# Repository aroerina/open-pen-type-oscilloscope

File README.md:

# open-pen-type-oscilloscope

ペンタイプオシロスコープ用の KiCad 基板設計データです。回路やスペックはDroidOscilloを踏襲しています。

このリポジトリには、回路図、PCB レイアウト、カスタムシンボル、カスタムフットプリント、3D モデル、製造用データを含みます。

.

## 概要

- KiCad プロジェクト: `USB_Oscilloscope.kicad_pro`
- 回路図: `USB_Oscilloscope.kicad_sch`
- PCB レイアウト: `USB_Oscilloscope.kicad_pcb`

- カスタムライブラリ: `ps_lib/`

## 関連リポジトリ

- ファームウェア: https://github.com/aroerina/DroidOscillo-Firmaware
- Android ホストアプリ: https://github.com/aroerina/DroidOscillo-Android_host
- 基板リポジトリ: https://github.com/aroerina/DoroidOscillo-Board

## 公開データ

回路図やガーバーファイルは、以下の Release ページにあります。

- https://github.com/aroerina/open-pen-type-oscilloscope/releases/tag/rev2.0

## 注意事項

- ファームウェア書き込みテストはまだ行っていません。かなり投げやり状態です。
- 製造や実装を行う前に、回路図、PCB、部品表、製造データを必ず確認してください。

## ライセンス

このハードウェア設計データは CERN Open Hardware Licence Version 2 - Permissive（CERN-OHL-P）で公開されています。

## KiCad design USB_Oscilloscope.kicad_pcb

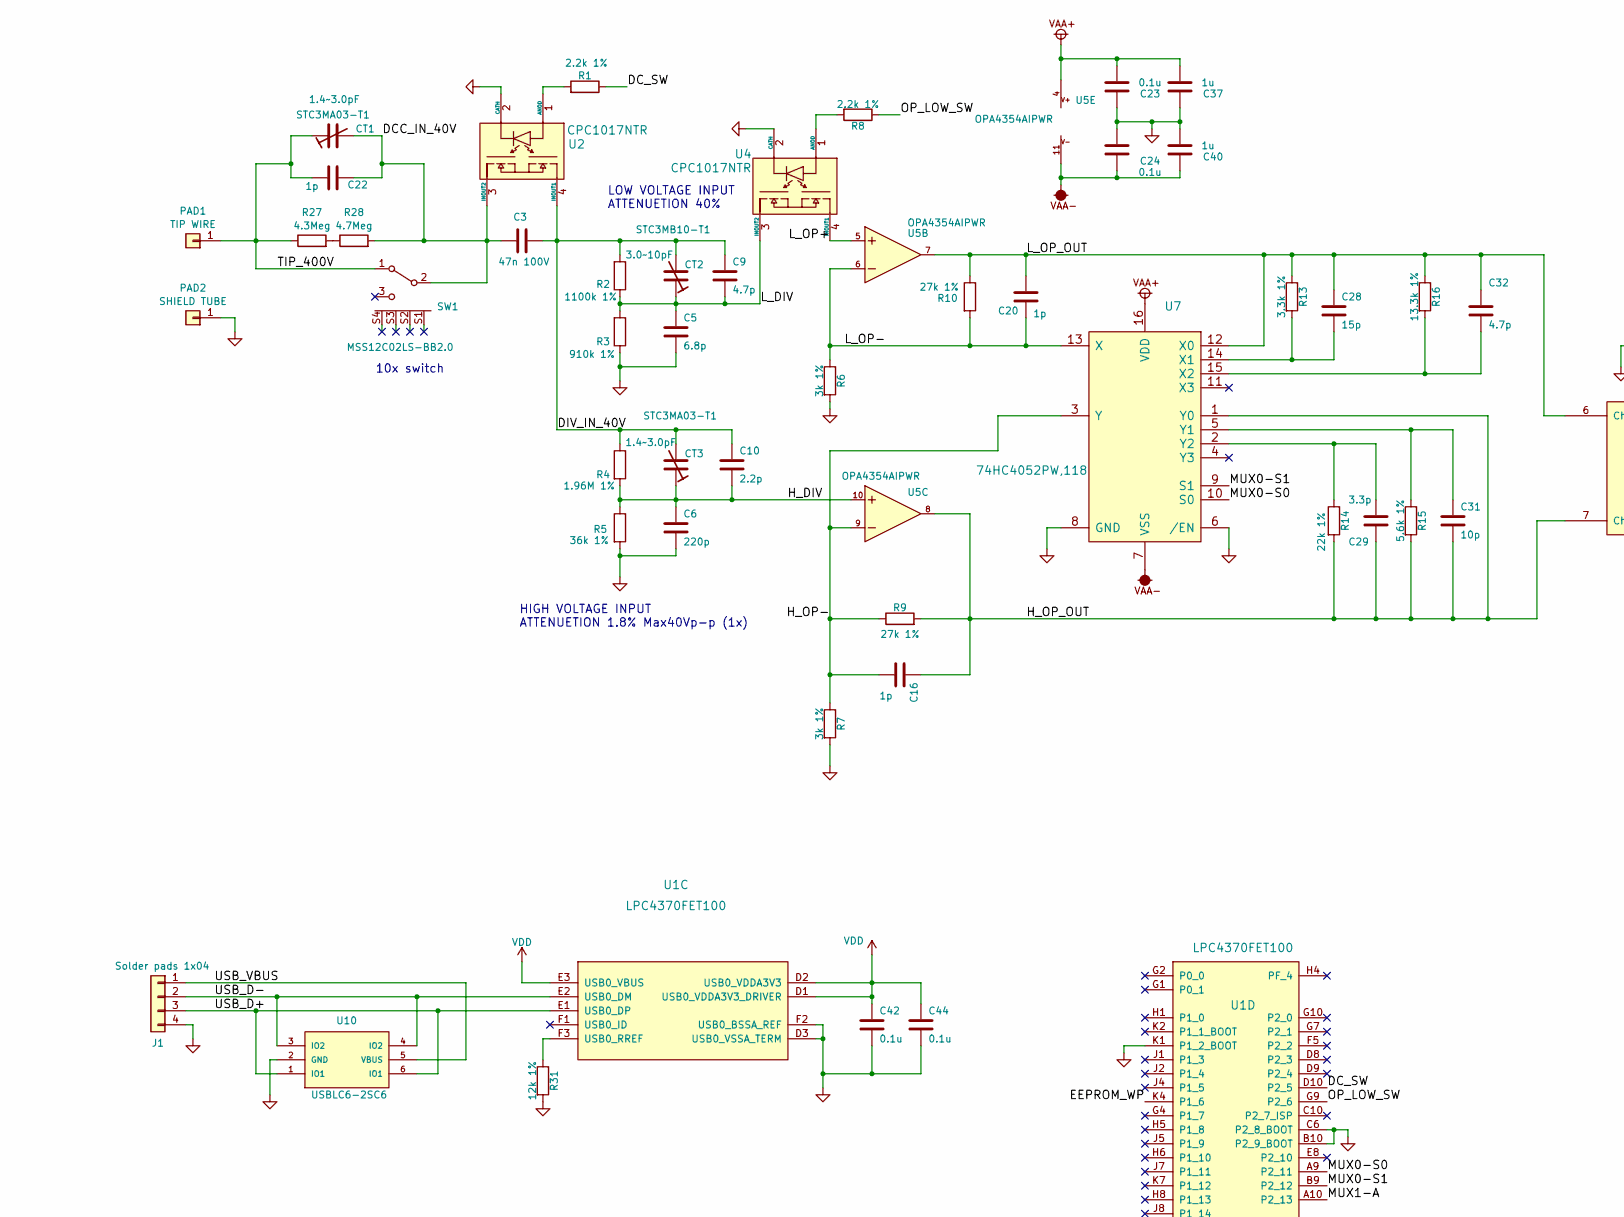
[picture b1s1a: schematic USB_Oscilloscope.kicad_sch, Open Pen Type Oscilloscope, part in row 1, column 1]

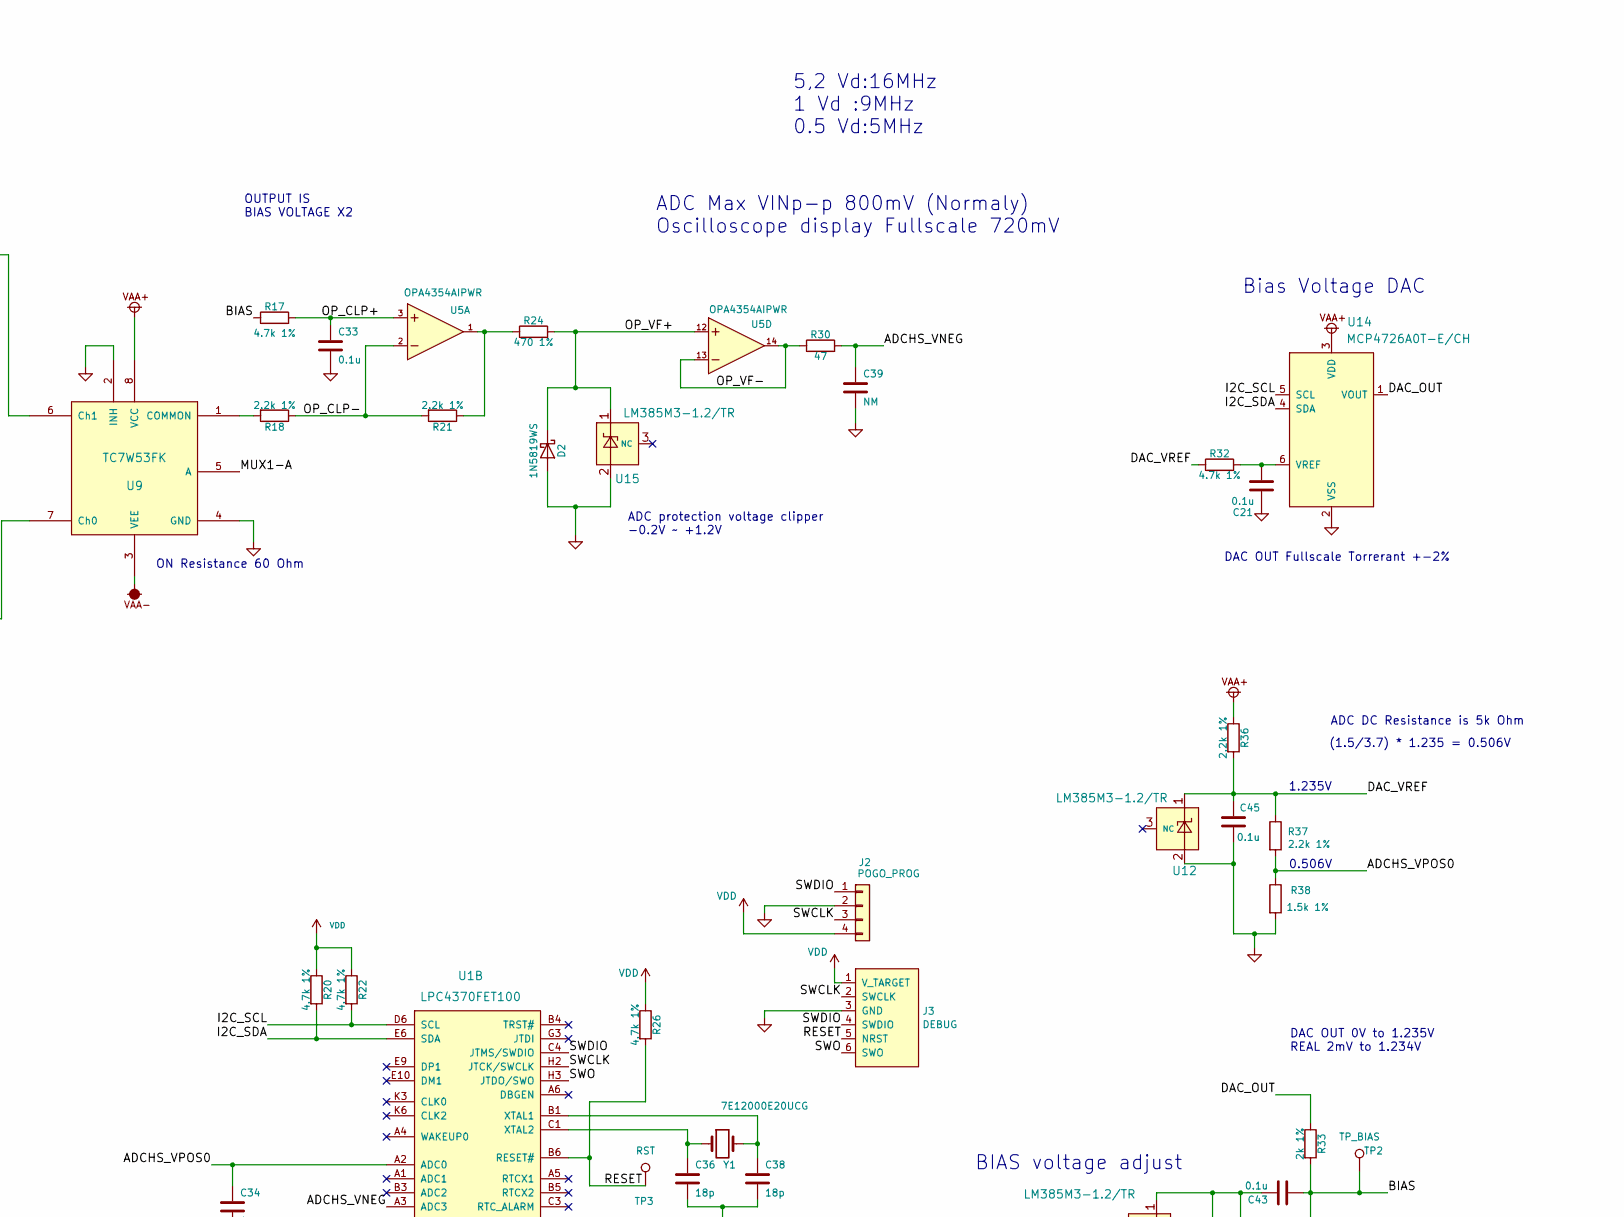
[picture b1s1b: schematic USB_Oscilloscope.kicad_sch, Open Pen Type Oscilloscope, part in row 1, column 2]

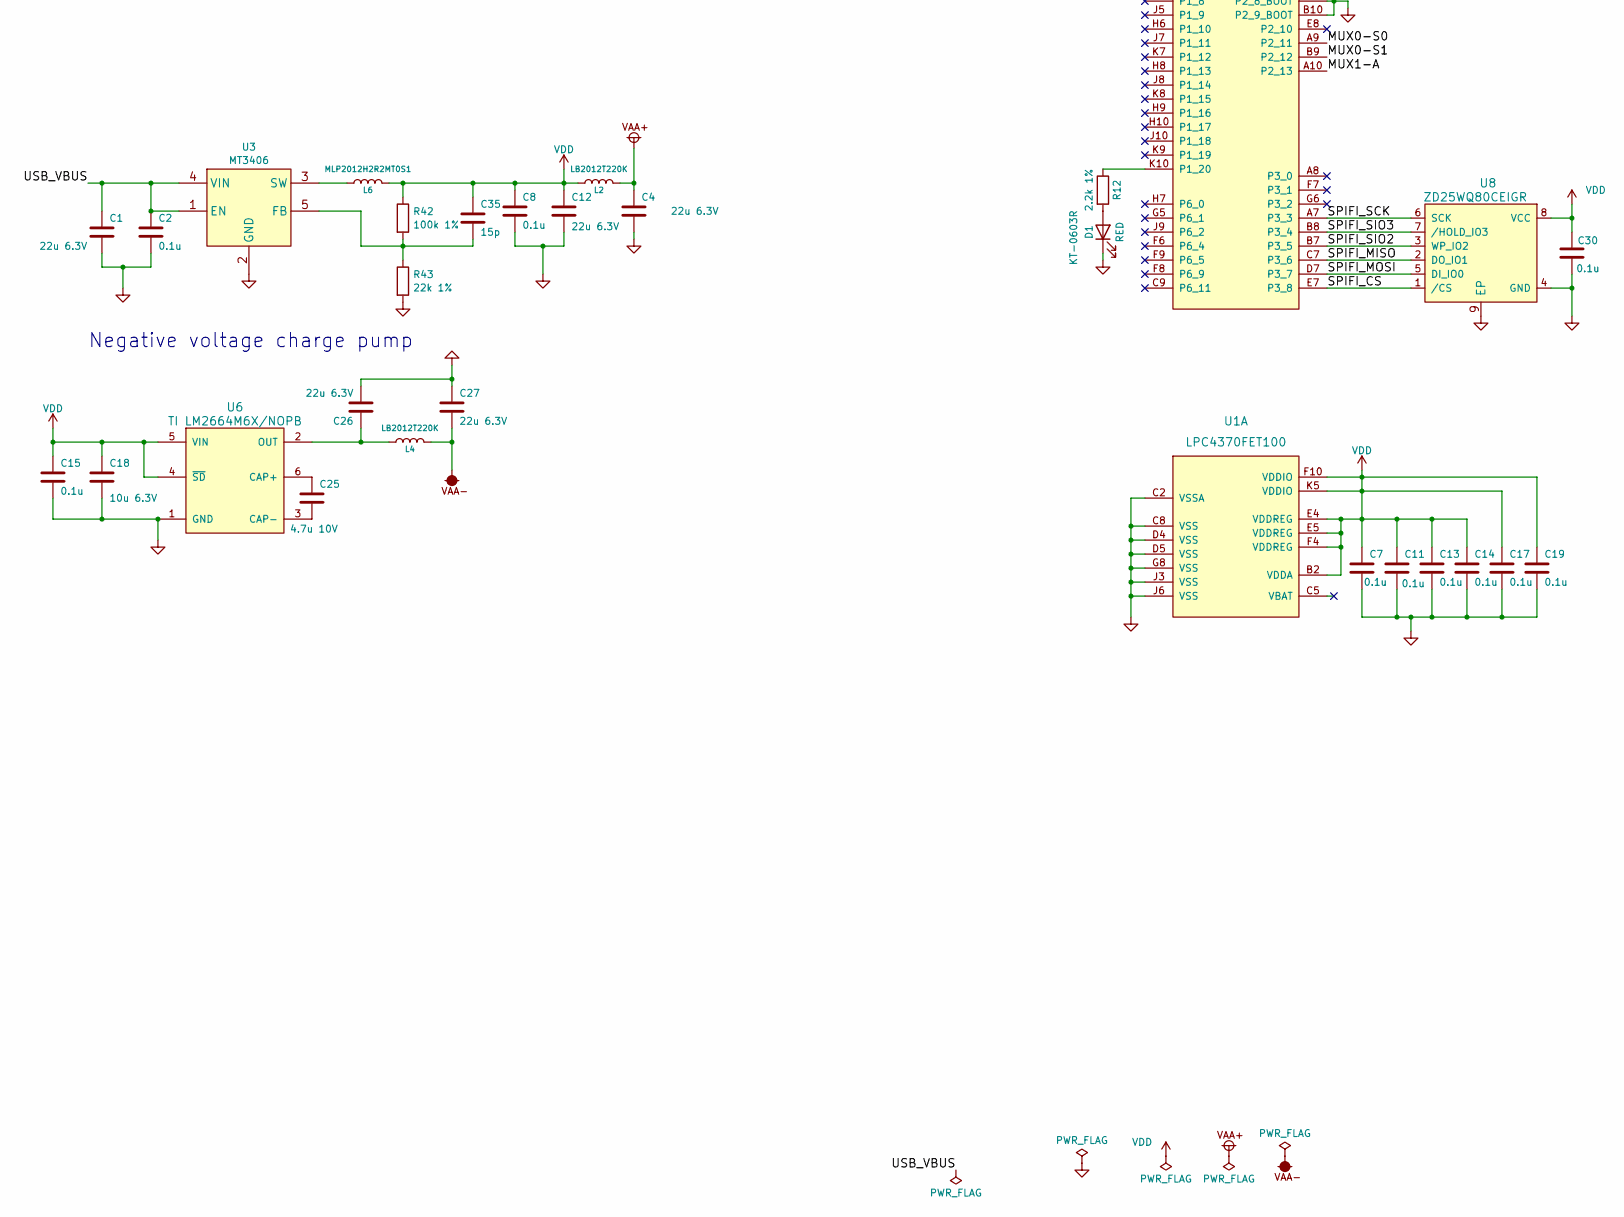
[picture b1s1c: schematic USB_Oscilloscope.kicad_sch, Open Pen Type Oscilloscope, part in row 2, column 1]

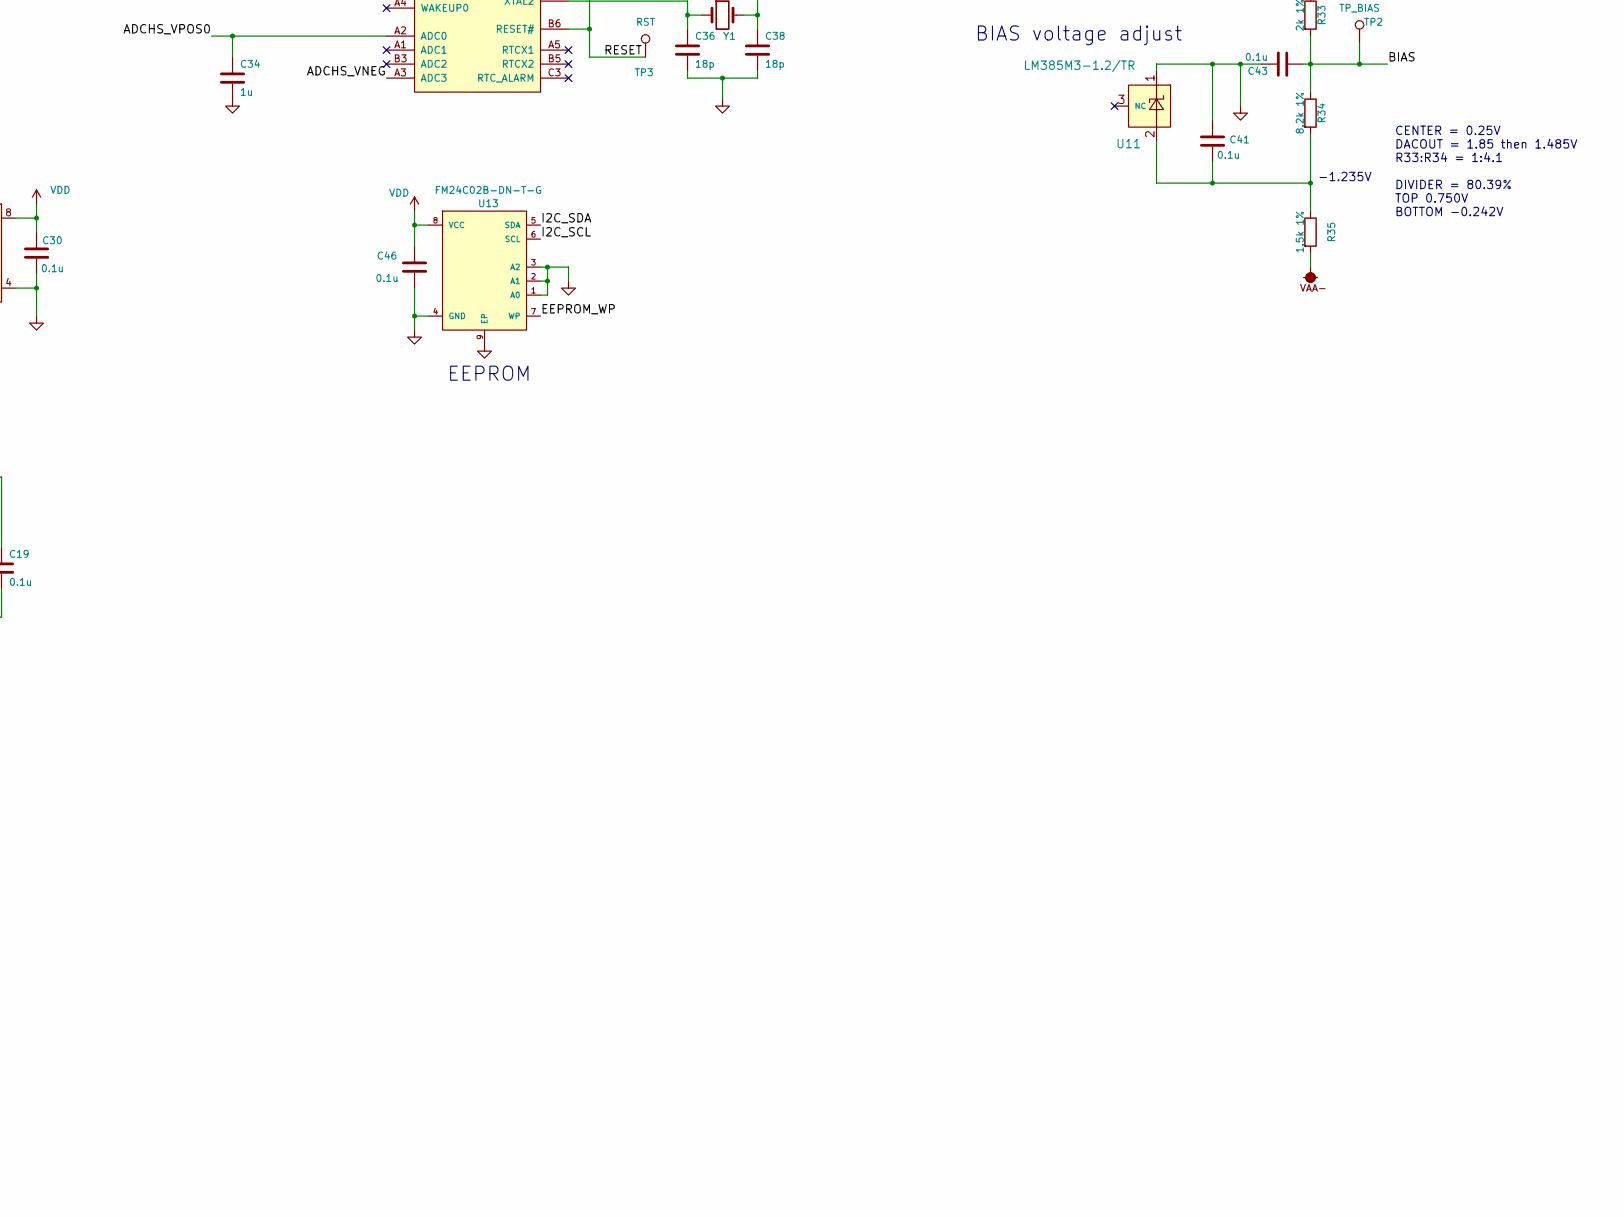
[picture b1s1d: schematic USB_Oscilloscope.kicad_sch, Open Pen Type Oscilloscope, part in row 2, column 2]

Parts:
C1, C4, C12, C26, C27: 22u 6.3V; C_0603_1608Metric; LCSC C59461
C2, C7, C8, C11, C13, C14, C15, C17, C19, C21, C23, C24, C30, C33, C41, C42, C43, C44, C45, C46: 0.1u; C_0402_1005Metric; LCSC C1525
C3: 47n 100V; C_0805_2012Metric; LCSC C107126
C5: 6.8p; C_0402_1005Metric; LCSC C1576
C6: 220p; C_0402_1005Metric; LCSC C1530
C9, C32: 4.7p; C_0402_1005Metric; LCSC C1569
C10: 2.2p; C_0402_1005Metric; LCSC C1559
C16, C20: 1p; C_0402_1005Metric; LCSC C1550
C18: 10u 6.3V; C_0402_1005Metric; LCSC C15525
C22: 1p; C_0603_1608Metric; LCSC C3890240
C25: 4.7u 10V; C_0402_1005Metric; LCSC C23733
C28, C35: 15p; C_0402_1005Metric; LCSC C1548
C29: 3.3p; C_0402_1005Metric; LCSC C1565
C31: 10p; C_0402_1005Metric; LCSC C32949
C34, C37, C40: 1u; C_0402_1005Metric; LCSC C52923
C36, C38: 18p; C_0402_1005Metric
C39: NM; C_0402_1005Metric
CT1, CT3: STC3MA03-T1; SHEWA STC03M; LCSC C22468119
CT2: STC3MB10-T1; SHEWA STC03M; LCSC C22468121
D1: KT-0603R; LED_0603_1608Metric; LCSC C2286
D2: 1N5819WS; D_SOD-323; LCSC C191023
J1: Solder pads 1x04; 01x04_wire_pads_Pitch2.0
J2: POGO_PROG; PIN_HEADER_P1.27x4
J3: DEBUG; JST_SH_SM06B-SRSS-TB_1x06-1MP_P1.00mm_Horizontal; LCSC C7430448
L2, L4: LB2012T220K; L_0805_2012Metric; LCSC C223253
L6: MLP2012H2R2MT0S1; L_0805_2012Metric; LCSC C383369
PAD1: TIP WIRE; TIP_WIRE
PAD2: SHIELD TUBE; pipe-out5.0_in4.0_len40.0
R1, R8, R12, R18, R21, R36, R37: 2.2k 1%; R_0402_1005Metric; LCSC C25879
R2: 1100k 1%; R_0402_1005Metric; LCSC C133039
R3: 910k 1%; R_0402_1005Metric; LCSC C25800
R4: 1.96M 1%; R_0402_1005Metric; LCSC C477601
R5: 36k 1%; R_0402_1005Metric; LCSC C43676
R6, R7: 3k 1%; R_0402_1005Metric; LCSC C25784
R9, R10: 27k 1%; R_0402_1005Metric; LCSC C25771
R13: 3.3k 1%; R_0402_1005Metric; LCSC C25890
R14, R43: 22k 1%; R_0402_1005Metric; LCSC C25768
R15: 5.6k 1%; R_0402_1005Metric; LCSC C25908
R16: 13.3k 1%; R_0402_1005Metric; LCSC C122547
R17, R20, R22, R26, R32: 4.7k 1%; R_0402_1005Metric; LCSC C25900
R24: 470 1%; R_0402_1005Metric; LCSC C25117
R27: 4.3Meg; R_0805_2012Metric; LCSC C17668
R28: 4.7Meg; R_0805_2012Metric; LCSC C17674
R30: 47; R_0402_1005Metric; LCSC C25118
R31: 12k 1%; R_0402_1005Metric; LCSC C25752
R33: 2k 1%; R_0402_1005Metric; LCSC C4109
R34: 8.2k 1%; R_0402_1005Metric; LCSC C25924
R35, R38: 1.5k 1%; R_0402_1005Metric; LCSC C25867
R42: 100k 1%; R_0402_1005Metric; LCSC C25741
SW1: MSS12C02LS-BB2.0; LCSC C3008585
TP2: TP_BIAS; TestPoint_Pad_D1.0mm
TP3: RST; TestPoint_Pad_D1.0mm
U1: LPC4370FET100; TFBGA-100_8x8mm_Layout10x10_P0.8mm; LCSC C1020255
U2, U4: CPC1017NTR; CPC1017N; LCSC C81521
U3: MT3406; SOT-23-5; LCSC C22462728
U5: OPA4354AIPWR; TSSOP-14_4.4x5mm_P0.65mm; LCSC C527494
U6: TI LM2664M6X/NOPB; SOT-23-6; LCSC C108573
U7: 74HC4052PW,118; TSSOP-16_4.4x5mm_P0.65mm; LCSC C5646
U8: ZD25WQ80CEIGR; Winbond_USON-8-1EP_3x2mm_P0.5mm_EP0.2x1.6mm; LCSC C16197313
U9: TC7W53FK; VSSOP-8_2.3x2mm_P0.5mm; LCSC C146370
U10: USBLC6-2SC6; SOT-23-6; LCSC C7519
U11, U12, U15: LM385M3-1.2/TR; SOT-23-3; LCSC C507206
U13: FM24C02B-DN-T-G; TDFN-8-1EP_3x2mm_P0.5mm_EP1.4x1.4mm; LCSC C250843
U14: MCP4726A0T-E/CH; SOT-23-6; LCSC C191581
Y1: 7E12000E20UCG; Crystal_SMD_2520-4Pin_2.5x2.0mm; LCSC C252259

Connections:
/ADCHS_VNEG: C39.1, R30.2, U1.A3 (ADC3)
/ADCHS_VPOS0: C34.1, R37.2, R38.1, U1.A2 (ADC0)
/BIAS: C43.2, R17.1, R33.2, R34.1, TP2.1
/DAC_OUT: R33.1, U14.1 (VOUT)
/DAC_VREF: C45.1, R32.1, R36.2, R37.1, U12.1
/DCC_IN_40V: C3.1, C22.1, CT1.2, R28.2, SW1.2 (B), U2.3 (INOUT2)
/DC_SW: R1.1, U1.D10 (P2_5)
/DIV_IN_40V: C3.2, C9.1, C10.1, CT2.2, CT3.2, R2.2, R4.1, U2.4 (INOUT1)
/EEPROM_WP: U1.K4 (P1_6), U13.7 (WP)
/H_DIV: C6.1, C10.2, CT3.1, R4.2, R5.1, U5.10 (+IN)
/H_OP-: C16.2, R7.1, R9.1, U5.9 (-IN), U7.3 (Y)
/H_OP_OUT: C16.1, C29.2, C31.2, R9.2, R14.2, R15.2, U5.8 (OUT), U7.1 (Y0), U9.7 (Ch0)
/I2C_SCL: R22.2, U1.D6 (SCL), U13.6 (SCL), U14.5 (SCL)
/I2C_SDA: R20.2, U1.E6 (SDA), U13.5 (SDA), U14.4 (SDA)
/L_DIV: C5.1, C9.2, CT2.1, R2.1, R3.2, U4.3 (INOUT2)
/L_OP+: U4.4 (INOUT1), U5.5 (+IN)
/L_OP-: C20.1, R6.1, R10.2, U5.6 (-IN), U7.13 (X)
/L_OP_OUT: C20.2, C28.1, C32.1, R10.1, R13.1, R16.1, U5.7 (OUT), U7.12 (X0), U9.6 (Ch1)
/MUX0-S0: U1.A9 (P2_11), U7.10 (S0)
/MUX0-S1: U1.B9 (P2_12), U7.9 (S1)
/MUX1-A: U1.A10 (P2_13), U9.5 (A)
/OP_CLP+: C33.1, R17.2, U5.3 (+IN)
/OP_CLP-: R18.1, R21.2, U5.2 (-IN)
/OP_LOW_SW: R8.1, U1.G9 (P2_6)
/OP_VF+: D2.1 (K), R24.2, U5.12 (+IN), U15.1
/OP_VF-: R30.1, U5.13 (-IN), U5.14 (OUT)
/RESET: J3.5 (NRST), R26.2, TP3.1, U1.B6 (RESET#)
/SPIFI_CS: U1.E7 (P3_8), U8.1 (/CS)
/SPIFI_MISO: U1.C7 (P3_6), U8.2 (DO_IO1)
/SPIFI_MOSI: U1.D7 (P3_7), U8.5 (DI_IO0)
/SPIFI_SCK: U1.A7 (P3_3), U8.6 (SCK)
/SPIFI_SIO2: U1.B7 (P3_5), U8.3 (WP_IO2)
/SPIFI_SIO3: U1.B8 (P3_4), U8.7 (/HOLD_IO3)
/SWCLK: J2.3, J3.2 (SWCLK), U1.H2 (JTCK/SWCLK)
/SWDIO: J2.1, J3.4 (SWDIO), U1.C4 (JTMS/SWDIO)
/SWO: J3.6 (SWO), U1.H3 (JTDO/SWO)
/TIP_400V: C22.2, CT1.1, PAD1.1, R27.1, SW1.1 (A)
/USB_D+: J1.3, U1.E1 (USB0_DP), U10.1 (IO1), U10.6 (IO1)
/USB_D-: J1.2, U1.E2 (USB0_DM), U10.3 (IO2), U10.4 (IO2)
/USB_VBUS: C1.1, C2.1, J1.1, U3.1 (EN), U3.4 (VIN), U10.5 (VBUS)
GND: C1.2, C2.2, C4.2, C5.2, C6.2, C7.2, C8.2, C11.2, C12.2, C13.2, C14.2, C15.2, C17.2, C18.2, C19.2, C21.2, C23.2, C24.1, C26.2, C27.1, C30.2, C33.2, C34.2, C36.2, C37.2, C38.2, C39.2, C40.1, C41.2, C42.2, C43.1, C44.2, C45.2, C46.2, D1.1 (K), D2.2 (A), J1.4, J2.2, J3.3 (GND), PAD2.1, R3.1, R5.2, R6.2, R7.2, R31.2, R38.2, R43.2, U1.B10 (P2_9_BOOT), U1.C2 (VSSA), U1.C6 (P2_8_BOOT), U1.C8 (VSS), U1.D3 (USB0_VSSA_TERM), U1.D4 (VSS), U1.D5 (VSS), U1.F2 (USB0_BSSA_REF), U1.G8 (VSS), U1.J3 (VSS), U1.J6 (VSS), U1.K1 (P1_2_BOOT), U2.2 (CATH), U3.2 (GND), U4.2 (CATH), U6.1 (GND), U7.6 (/EN), U7.8 (GND), U8.4 (GND), U8.9 (EP), U9.2 (INH), U9.4 (GND), U10.2 (GND), U11.1, U12.2, U13.1 (A0), U13.2 (A1), U13.3 (A2), U13.4 (GND), U13.9 (EP), U14.2 (VSS), U15.2
unnamed: C41.1, R34.2, R35.1, U11.2
unnamed: D1.2 (A), R12.2
unnamed: R27.2, R28.1
unnamed: C38.1, U1.B1 (XTAL1), Y1.2
unnamed: C36.1, U1.C1 (XTAL2), Y1.1
unnamed: R31.1, U1.F3 (USB0_RREF)
unnamed: R12.1, U1.K10 (P1_20)
unnamed: R1.2, U2.1 (ANOD)
unnamed: C35.2, R42.2, R43.1, U3.5 (FB)
unnamed: L6.1, U3.3 (SW)
unnamed: R8.2, U4.1 (ANOD)
unnamed: R21.1, R24.1, U5.1 (OUT)
unnamed: C25.1, U6.6 (CAP+)
unnamed: C25.2, U6.3 (CAP-)
unnamed: C26.1, L4.1, U6.2 (OUT)
unnamed: C28.2, R13.2, U7.14 (X1)
unnamed: C32.2, R16.2, U7.15 (X2)
unnamed: C31.1, R15.1, U7.5 (Y1)
unnamed: C29.1, R14.1, U7.2 (Y2)
unnamed: R18.2, U9.1 (COMMON)
unnamed: C21.1, R32.2, U14.6 (VREF)
VDD: C7.1, C8.1, C11.1, C12.1, C13.1, C14.1, C15.1, C17.1, C18.1, C19.1, C30.1, C35.1, C42.1, C44.1, C46.1, J2.4, J3.1 (V_TARGET), L2.1, L6.2, R20.1, R22.1, R26.1, R42.1, U1.B2 (VDDA), U1.D1 (USB0_VDDA3V3_DRIVER), U1.D2 (USB0_VDDA3V3), U1.E3 (USB0_VBUS), U1.E4 (VDDREG), U1.E5 (VDDREG), U1.F4 (VDDREG), U1.F10 (VDDIO), U1.K5 (VDDIO), U6.4 (~SD), U6.5 (VIN), U8.8 (VCC), U13.8 (VCC)
alt_VAA+: C4.1, C23.1, C37.1, L2.2, R36.1, U5.4 (V+), U7.16 (VDD), U9.8 (VCC), U14.3 (VDD)
alt_VAA-: C24.2, C27.2, C40.2, L4.2, R35.2, U5.11 (V-), U7.7 (VSS), U9.3 (VEE)

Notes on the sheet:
HIGH VOLTAGE INPUT ATTENUETION 1.8% Max40Vp-p (1x)
Bias Voltage DAC
EEPROM
-1.235V
DAC OUT 0V to 1.235V REAL 2mV to 1.234V
10x switch
0.506V
CENTER = 0.25V DACOUT = 1.85 then 1.485V R33:R34 = 1:4.1 DIVIDER = 80.39% TOP 0.750V BOTTOM -0.242V
LOW VOLTAGE INPUT ATTENUETION 40%
5,2 Vd:16MHz 1 Vd :9MHz 0.5 Vd:5MHz
ADC DC Resistance is 5k Ohm
Negative voltage charge pump
ON Resistance 60 Ohm
OUTPUT IS BIAS VOLTAGE X2
ADC protection voltage clipper -0.2V ~ +1.2V
1.235V
(1.5/3.7) * 1.235 = 0.506V
ADC Max VINp-p 800mV (Normaly) Oscilloscope display Fullscale 720mV
DAC OUT Fullscale Torrerant +-2%
BIAS voltage adjust

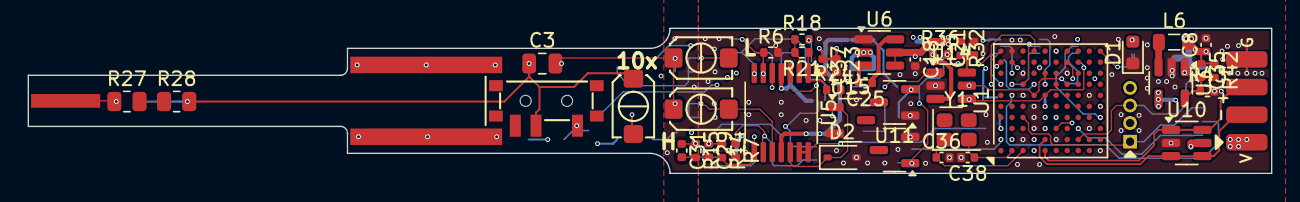
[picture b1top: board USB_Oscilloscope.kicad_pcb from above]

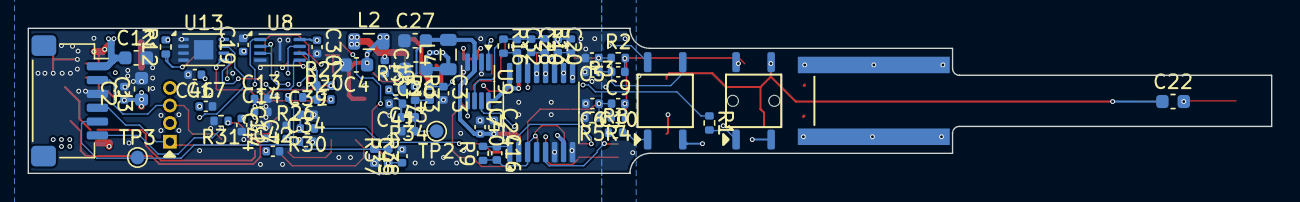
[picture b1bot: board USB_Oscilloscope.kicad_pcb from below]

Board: 4 copper layers, 90.0 x 10.5 mm, 113 parts (67 on the bottom side), 65 nets.

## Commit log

2025-09-18 回路図 DRC pass
2025-09-22 プロジェクト名変更
2025-12-14 ペン型オシロに変更
2025-12-14 古い回路図を削除
2025-12-14 gabarフォルダを削除
2026-05-28 readme.mdを作成
2026-05-28 画像を追加
